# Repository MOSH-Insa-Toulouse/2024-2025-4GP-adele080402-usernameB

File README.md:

# PROJET CAPTEUR

## Sommaire
- [Description du projet](#description-du-projet)
- [Livrables](#livrables)
- [Matériel utilisé](#matériel-utilisé)
- [Simulation du montage sur LTSpice](#simulation-du-montage-sur-ltspice)
- [Création du PCB](#création-du-pcb)  
    -[KiCad](#kicad)  
    -[Schéma complet](#kicad)  
    -[Impression du PCB](#impression-du-pcb)  
- [Code Arduino](#code-arduino)
- [Application Android](#application-android)
- [Datasheet](#datasheet)
- [Tests de notre capteur et relevé de valeurs](#tests-de-notre-capteur-et-relevé-de-valeurs)
- [Contact](#contact)

## Description du projet

Nous avons réalisé ce projet dans le cadre de l'UF "du capteur au banc de test en open source hardware", en 4ème année de Génie Physique à l'INSA de Toulouse.
Le but de ce projet, basé sur l'article "Pencil Drawn Strain Gauges and Chemiresistors on Paper" (Cheng-Wei Lin, Zhibo Zhao, Jaemyung Kim & Jiaxing Huang), est de réaliser et tester un capteur low-tech, et d'évaluer son fonctionnement par rapport à un capteur commercialisé, afin de voir s'il est lui-même industrialisable. Le capteur concerné s'apparente à une jauge de contrainte, réalisée avec du papier recouvert d'une couche de graphite.  
Pour ce faire, nous avons réalisé un PCB à partir du logiciel KiCad, que nous avons pu intégrer à une carte Arduino UNO. Cela nous a permis d'effectuer des mesures et de tester notre capteur.

## Livrables

- PCB Shield adapté à l'Arduino Uno
- Code Arduino complet
- Banc de test du capteur
- Application Android fonctionnant par Bluetooth
- Datasheet du capteur

## Matériel utilisé

- Écran OLED : SSD1306
- Flex sensor
- Capteur Graphène
- Encodeur Rotatoire : KY-040
- Module Bluetooth HC-05
- Amplificateur Opérationnel : LCT-1050
- Potentiomètre Digital : MCP 41050
- Résistances : 1kOhms, 10kOhms, 100kOhms
- Capacités : 2x100nF, 1x1uF

## Simulation du montage sur LTSpice

Avant de commencer la réalisation concrète de notre projet, nous avons réalisé le montage qui sera réalisé physiquement sur [LTSpice](./LTSpice). Cette simulation nous a permis de comprendre comment l'arduino Uno pouvait acquérir les données du capteur. En effet, sans mettre en place un circuit transimpédance, nous ne serions pas en capacité d'acquérir des valeurs de résistance aussi élevées (k-M Ohms), puisque le courant résultant à acquérir avec un générateur 5V est très faible.

## Création du PCB
### KiCad

Pour commencer le projet, nous avons dû nous familiariser avec le logiciel KiCad. Au début, nous avons eu du mal à assimiler les différentes étapes à effectuer, à cause de la diversité de ces dernières dans le logiciel KiCad. Nous avons finalement réussi à imprimer notre PCB dans les temps et sans problème. 
Premièrement, nous avons dû reprendre le circuit que nous avions réalisé sur LTSpice qui simulait le circuit final.  

Nous avons pris ce modèle pour réaliser la [partie schématique](./KiCad-Shield-Uno-FlexSensor) sur KiCad. Nous avons modélisé le circuit amplificateur, ainsi que différents dispositifs également présents sur notre PCB : 

- le [potentiomètre digital](./KiCad-Shield-Uno-FlexSensor/MaLibrairieEmpreinte.pretty)  

- l'[encodeur rotatoire](./KiCad-Shield-Uno-FlexSensor/MaLibrairieEmpreinte.pretty) 

- l'[écran OLED](./KiCad-Shield-Uno-FlexSensor/MaLibrairieEmpreinte.pretty)

- le [module Bluetooth](./KiCad-Shield-Uno-FlexSensor/MaLibrairieEmpreinte.pretty)
  
- l'[amplificateur opérationnel LTC41050](./KiCad-Shield-Uno-FlexSensor/MaLibrairieEmpreinte.pretty)

Ensuite, lorsque nous avons terminé le schématique, nous avons pu passer à l'organisation des éléments du PCB. Après avoir créé les empreintes et importer les bons modèles 3D des différents éléments, nous avons dû disposer de manière la plus optimale ces derniers. Cette étape a été un peu longue et nous avons dû recommencer plusieurs fois afin de limiter le nombre de vias et trouver la meilleure organisation possible. Nous avons finalement réussi à réaliser notre PCB avec seulement 3 vias. Nous avons également utilisé un plan de masse afin de simplifier le circuit.   
Une fois validé, nous avons pu passer à l'impression.

### Schéma complet

                                            Schématique du PCB

                                          Routage terminé du PCB

                                          Modèle 3D du PCB (face avant)

                                          Modèle 3D du PCB (face arrière)

### Impression du PCB

Pour imprimer le PCB, nous avons dû télécharger le fichier [.gerber](./KiCad-Shield-Uno-FlexSensor/Gerber/KiCad-Shield-Uno-FlexSensor-B_Cu.pdf). Nous avons envoyé tous nos fichiers KiCad à Catherine Crouzet, qui nous a donné rendez-vous au GEI. Sur place, elle nous a expliqué toute la procédure. Le développement a été fait grâce au masque (fichier Gerber) placé sur une plaquette vierge et passé aux UVs, puis aux bains de développement.  
Une fois la plaquette dessinée, nous sommes allées percer la plaquette (les diamètres sont de 0,8mm pour les composants, et 1mm pour les pins de l'Arduino) sur laquelle nous avons soudé tous les composants. Cette partie était relativement rapide.

                                             Fichier Gerber

                                              PCB imprimé

                                      PCB avec les composants soudés

## Code Arduino

Nous avons ensuite rédigé le [code](./arduino_code_capteur/arduino_code_capteur.ino) .ino, écrit en C++.   
Pour ce faire, nous nous sommes inspirées des codes étudiés durant les TPs/TDs tout au long du deuxième semestre, qui nous ont permis de mieux comprendre comment fonctionnait chaque composant.  
Nous avons rédigé les codes de chaque composant indépendamment afin de pouvoir les tester un à un, puis nous avons écrit le code en rajoutant peu à peu les codes fonctionnels et en les reliant les uns aux autres.

Le plus difficile à coder était l'encodeur rotatoire. Nous avons essayé de nombreuses fois, en nous inspirant des codes des années précédentes, ou des codes présents sur internet comme [Passion Électronique](https://passionelectronique.fr/encodeur-rotatif-incremental-mecanique/).  
Cependant, nous n'avons pas réussi à écrire un code fonctionnel qui nous permettait de naviguer entre les menus que nous avions créés. Nous avons décidé de garder les menus pour les différents composants (flex sensor, graphite sensor et potentiomètre digital) dans le code, pour pouvoir y accéder si besoin, ainsi que si de prochaines personnes voulaient essayer de rajouter la navigation entre les menus.   
Nous avons néanmoins voulu utiliser l'encodeur rotatoire, donc nous avons ajouté une fonction permettant de faire varier la valeur du potentiomètre digital grâce à l'encodeur.  

Nous n'avons malheureusement pas eu le loisir d'être très créatives car nous avons passé beaucoup de temps à décortiquer le fonctionnement et l'écriture du code pour chaque composant. Nous avons tout de même souhaité personnaliser notre projet en rajoutant un écran d'accueil à l'initialisation de l'écran OLED, qu'on peut voir sur la photo ci-dessous. 

                                              Écran d'accueil de l'OLED

## Application Android

Pour l'[application Android](./Application Android), nous avons rencontré de nombreux problèmes au cours de son développement sur [MIT App Inventor](https://appinventor.mit.edu/). Le premier était simplement un problème d'affichage des données récupérer sur le graphique intéractif. Mais par la suite, nous ne pouvions même plus connecter notre téléphone à l'application, ce qui a nettement ralenti le développement de cette dernière, ainsi que son résultat final.  
Nous avons finalement une application à laquelle nous pouvons nous connecter, qui récupère les données affichées simultanément sur l'écran OLED, trace un graphique en temps réel, et contient un bouton RESET.

                                              Interface de l'application Android

## Datasheet

Pour écrire la [datasheet](./Datasheet_capteur.pdf), nous avons décrit toutes les spécifités de notre capteur, tout en essayant de bien en expliquer son fonctionnement. Nous nous sommes basées sur les datasheets que nous avons pu étudier en cours au début du semestre, ainsi que toutes celles utilisées dans le cadre de nos études ou vies personnelles. La datasheet donne également un exemple d'application que l'on a expérimenté  au cours de ce projet.

## Tests de notre capteur et relevé de valeurs

Pour les relevés de valeur, nous avons rencontré un problème de consistance dans les mesures.
Le banc de test n'étant pas disponible lors de nos relevés de mesure, nous avons dû improviser et tester le capteur avec des objets circulaires dont le diamètre variait suffisamment pour avoir des données pertinentes. Ci-dessous est une photo des objets que nous avons utilisés.

                                        Objets utilisés pour le banc de test et leurs diamètres

Nous avons essayé de suivre un protocole de mesure afin d'avoir les mesures les plus pertinentes possible. Cependant, nous n'avons pas eu des mesures très satisfaisantes. 
Plus la mine de crayon est dure (2H), plus le capteur va être sensible et les valeurs vont fluctuer significativement, alors même que le capteur est immobile et qu'on n'y applique aucune déformation.
Inversement, plus la mine de crayon est grasse (6B), moins le capteur va être sensible et les valeurs vont rester très stables. On n'observera donc aucun changement de résistance, même en appliquant une forte déformation.

Aussi la manière de déposer le graphite influence beaucoup les valeurs obtenues.

Nous avons réussi à relever des valeurs uniquement pour les mines B et HB. Pour les autres mines testées, les valeurs n'étaient malheureusement pas pertinentes.

- HB : Mine avec laquelle le relevé de données a été concluant en compression mais moins en extension.
- B : Mine avec laquelle le relevé de données a été le plus concluant.
- 6B :Les valeurs de résistance mesurées avec cette mine restent bloquées à une valeur :  à 650 MOhms, même si la déformation appliquée est très importante.
- 2H : Les valeurs de résistance mesurées fluctuent trop, nous ne parvenons pas à avoir de données stables.

## Contact

Pour toute question ou information complémentaire, vous pouvez nous contacter :  
•Adèle Hovnanian, hovnanian@insa-toulouse.fr  
•Lola Grammont, grammont@insa-toulouse.fr

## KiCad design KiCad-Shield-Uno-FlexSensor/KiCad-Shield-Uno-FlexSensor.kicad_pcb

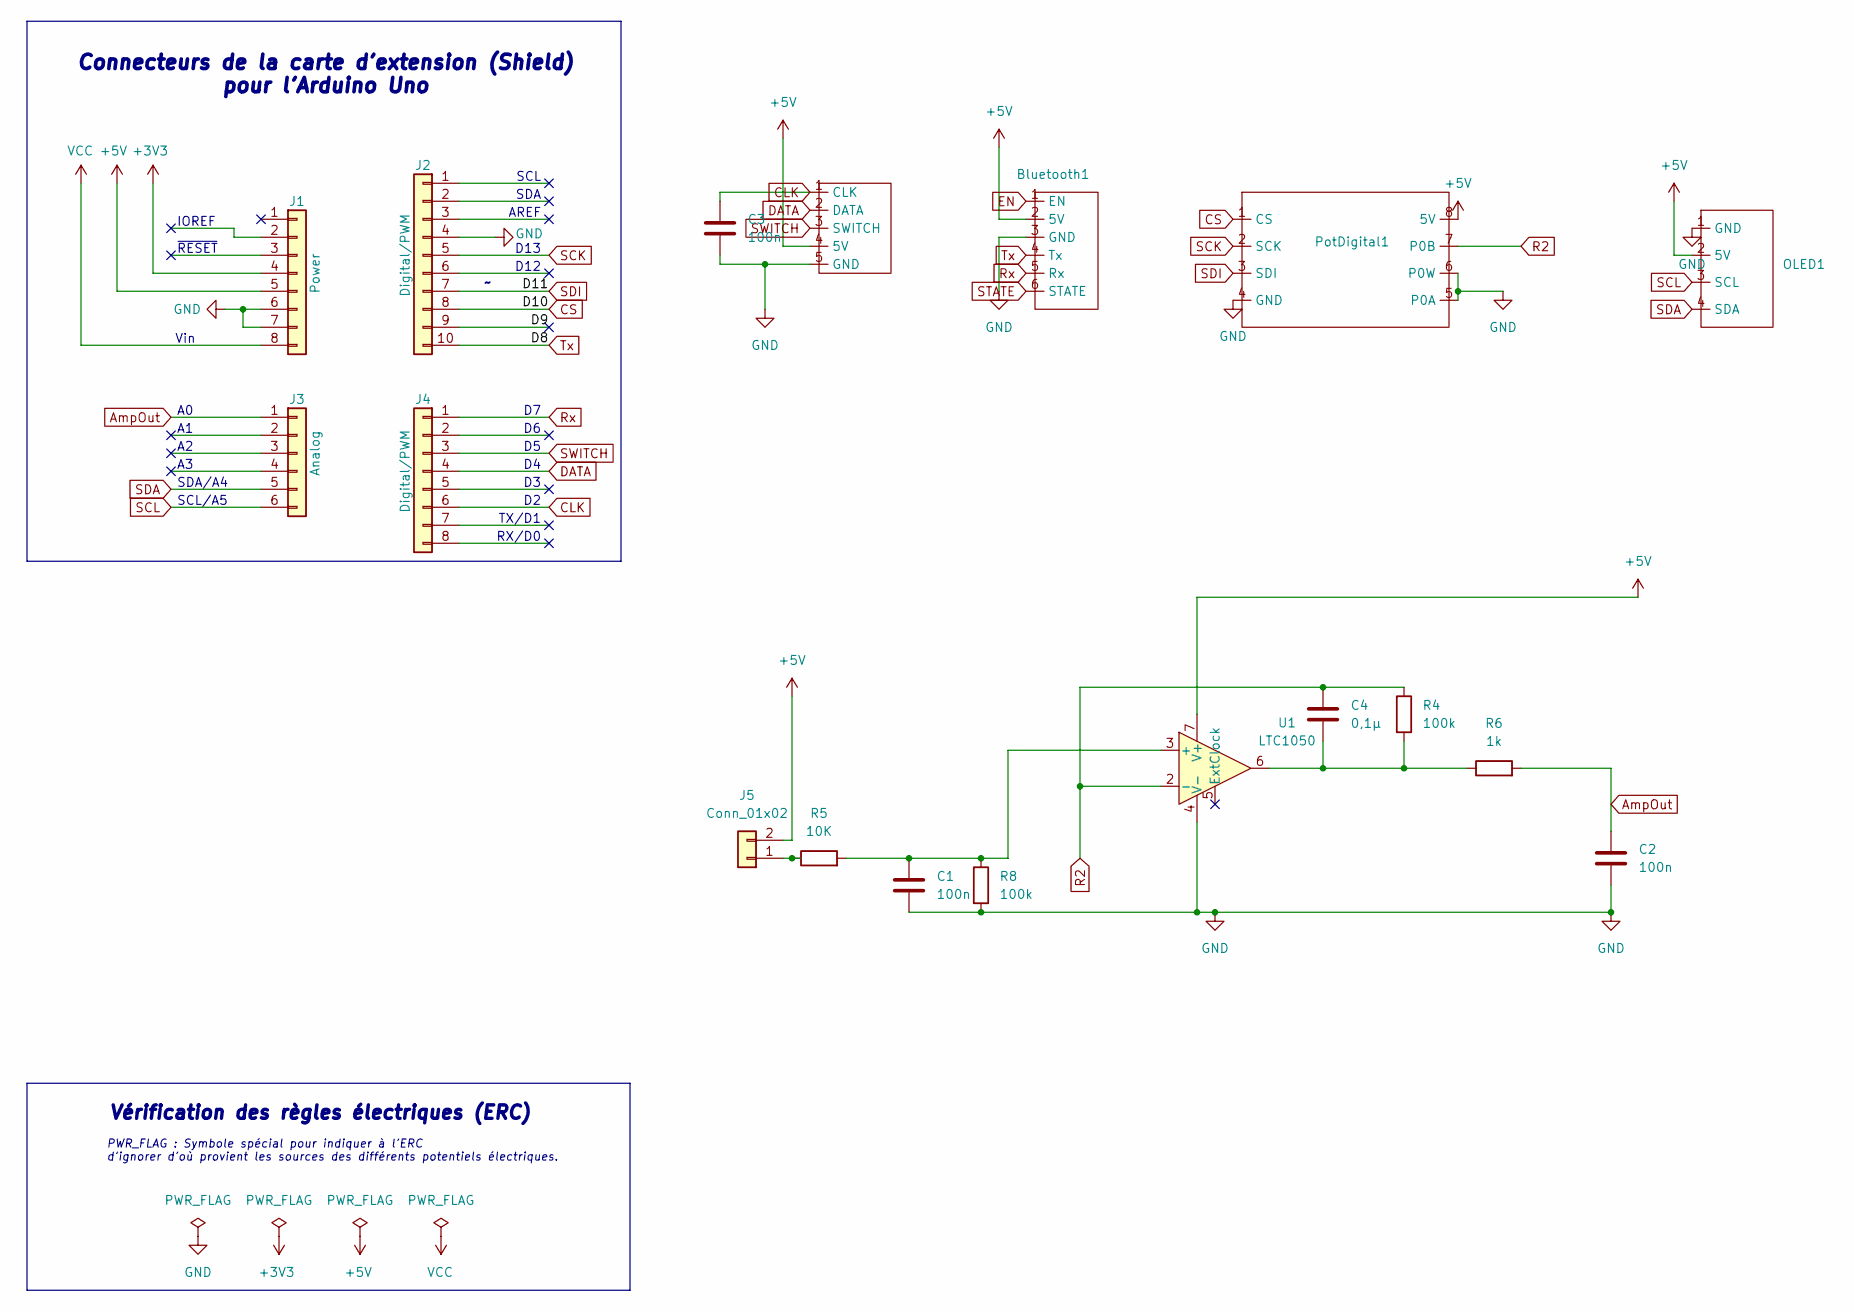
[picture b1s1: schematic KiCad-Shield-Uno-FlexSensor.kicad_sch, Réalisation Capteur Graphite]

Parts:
Bluetooth1: Bluetooth
C1, C2, C3: 100n; C_Disc_D6.0mm_W2.5mm_P5.00mm
C4: 0,1µ; C_Rect_L9.0mm_W5.1mm_P7.50mm_MKT
Encodeur_rotatoire1: EncodeurRotatoire
J1: Power; PinSocket_1x08_P2.54mm_Vertical
J2: Digital/PWM; PinSocket_1x10_P2.54mm_Vertical
J3: Analog; PinSocket_1x06_P2.54mm_Vertical
J4: Digital/PWM; PinSocket_1x08_P2.54mm_Vertical
J5: Conn_01x02; PinSocket_1x02_P2.54mm_Vertical
OLED1: OLED
PotDigital1: PotDigital
R4, R8: 100k; R_Axial_DIN0207_L6.3mm_D2.5mm_P10.16mm_Horizontal
R5: 10K; R_Axial_DIN0207_L6.3mm_D2.5mm_P10.16mm_Horizontal
R6: 1k; R_Axial_DIN0207_L6.3mm_D2.5mm_P10.16mm_Horizontal
U1: LTC1050; LTC41050

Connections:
+3V3: J1.4
+5V: Bluetooth1.2 (5V), Encodeur_rotatoire1.4 (5V), J1.5, J5.2, OLED1.2 (5V), PotDigital1.8 (5V), U1.7 (V+)
/D9: J2.9
AmpOut: C2.1, J3.1, R6.2
CLK: C3.1, Encodeur_rotatoire1.1 (CLK), J4.6
CS: J2.8, PotDigital1.1 (CS)
DATA: Encodeur_rotatoire1.2 (DATA), J4.4
EN: Bluetooth1.1 (EN)
GND: Bluetooth1.3 (GND), C1.2, C2.2, C3.2, Encodeur_rotatoire1.5 (GND), J1.6, J1.7, J2.4, OLED1.1 (GND), PotDigital1.4 (GND), PotDigital1.5 (P0A), PotDigital1.6 (P0W), R8.2, U1.4 (V-)
unnamed: C4.2, R4.2, R6.1, U1.6
unnamed: J5.1, R5.1
unnamed: C1.1, R5.2, R8.1, U1.3 (+)
R2: C4.1, PotDigital1.7 (P0B), R4.1, U1.2 (-)
Rx: Bluetooth1.5 (Rx), J4.1
SCK: J2.5, PotDigital1.2 (SCK)
SCL: J3.6, OLED1.3 (SCL)
SDA: J3.5, OLED1.4 (SDA)
SDI: J2.7, PotDigital1.3 (SDI)
STATE: Bluetooth1.6 (STATE)
SWITCH: Encodeur_rotatoire1.3 (SWITCH), J4.3
Tx: Bluetooth1.4 (Tx), J2.10
VCC: J1.8

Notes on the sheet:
AREF
SDA/A4
D12
~{RESET}
RX/D0
TX/D1
D13
Vin
SDA
Vérification des règles électriques (ERC)
Connecteurs de la carte d'extension (Shield) pour l'Arduino Uno
SCL/A5
SCL
IOREF
PWR_FLAG : Symbole spécial pour indiquer à l'ERC d'ignorer d'où provient les sources des différents potentiels électriques.

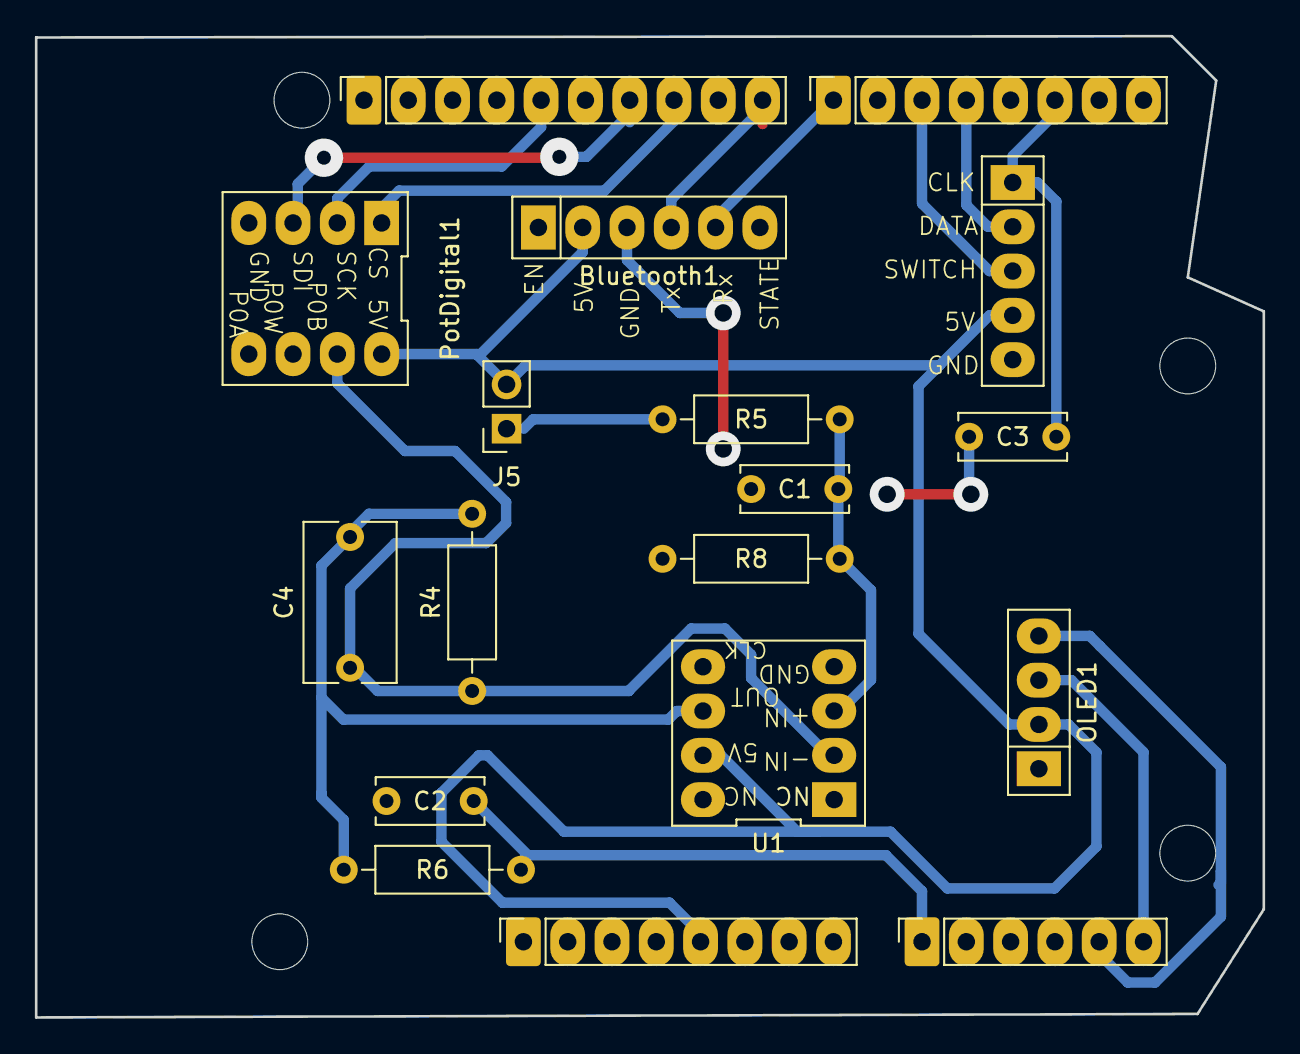
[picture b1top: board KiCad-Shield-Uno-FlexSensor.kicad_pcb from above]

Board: 2 copper layers, 70.4 x 56.3 mm, 22 parts (0 on the bottom side), 17 nets.

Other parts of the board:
MH1, MH2, MH3, MH4: MountingHole_3.2mm

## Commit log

2025-02-21 Ajout de ma todolist
2025-02-21 Ajout d'un item à ma liste
2025-03-28 Fichiers Kicad finaux
2025-04-08 Commencement du code pour l'arduino
2025-04-19 test
2025-04-19 commencement de l'écriture du fichier README
2025-04-19 nettoyage dossier
2025-04-19 écriture README
2025-05-15 rajout de quelques modifs fichier README
2025-05-22 rajout datasheet
2025-05-23 Ajout d'images
2025-05-23 Images déplacées
2025-05-27 Rename IMG_1794.jpg to PCB_imprime.jpg
2025-05-27 Rename Capture d'écran 2025-03-28 103607.png to Routage_kicad.png
2025-05-27 Rename Capture d'écran 2025-03-28 103658.png to Schematique_kicad.png
2025-05-27 Rename Capture d'écran 2025-03-28 103821.png to Montage_3D.png
2025-05-27 Rename Capture d'écran 2025-03-28 103835.png to PCB_kicad.png
2025-05-27 Mise à jour du code
2025-05-27 mise à jour readme
2025-05-27 Ajout d'image
2025-05-27 Rename IMG_2122.png to Banc_de_test.png
2025-05-27 Rajout de l'application et misde à jour du code
2025-05-28 Nettoyage des fichiers
2025-05-28 màj readme
2025-05-28 Rajout photos
2025-05-28 rajout photo
2025-05-28 modification readme
2025-05-28 Rename Capture d'écran 2025-05-27 215414.png to Blocs_de_code.png
2025-05-28 Rename Capture d'écran 2025-05-27 215338.png to Blocs_de_code_1.png
2025-05-28 Rename Blocs_de_code.png to Blocs_de_code_2.png
2025-05-28 Rename 1748431283842.jpg to Écran_app.jpg
2025-05-28 Rename Écran_app.jpg to Écran_app_vierge.jpg
2025-05-28 Rename 1748431283830.jpg to Écran_app_graphe.jpg
2025-05-28 Rename Capture d’écran 2025-05-28 à 15.44.57.png to Écran_app_graphe_bonformat.png
2025-05-28 rajout relevé valeurs
2025-05-28 Rename to Écran_app_graphe.png
2025-05-28 modif photos
